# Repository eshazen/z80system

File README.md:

# z80system
Yet another home-brew z80 system

This project has diverged a lot from my original plan to build a
from-scratch portable Z80 system.  I may yet do that.  Meanwhile I
have an RC2014 system ~~running happily~~ which is very flaky.

## New thoughts in 2024

* See [DevLog2024](DevLog2024.md)

Ordered:

* SC131 complete kit
* 3x Z80 chips
* New EEPROM programmer PCB for Arduino Mega 2560
* A few more 32kx8 flash and some 512kx8 RAMs

Renewed interest in:

* A homebrew system with at least some retro features
* Rock-solid operation
* Two console options:
  * UART (FTDI) to PC
  * Keyboard and video (both UART also?)
* Easy interface for backup / file transfer (Ethernet, UART, other)
  (Ethernet ENC28J60, see below)
* IDE Hard drive (not sure why I'm obsessed with this!).  Could be SSD.
* VGA-class video, eventually with pixel graphics
* Possible ICom floppy interface (8255)

Not so interested in building all the peripherals (SIO, DMA, CTC) and
MMU so a Z180 seems like a nice option.  Will start with SC131 to get experience
with Z180.

### Buffered expansion bus

* I/O (any address above FF)
* Memory access at least 64k

Would like to minimise the gate delays in decoding the data bus enable,
so maybe just use A18, A19 for memory decode and A15 for IO decode.
74AHC139 + 74AHC32 = ~15ns max delay.

## What works now

* [FPGA_VGA](https://github.com/eshazen/z80system/tree/master/hardware/rc2014_vga) -
  RC2014 board hosting an FPGA module for VGA text video
* [FPGA_firmware](https://github.com/eshazen/vga_terminal) - firmware
  (Xilinx Vivado) for above
* [Keyboard](https://github.com/eshazen/z80system/tree/master/hardware/keyboard/minimal-60-v3) -
  60% keyboard with serial output
* [AVR_Code](https://github.com/eshazen/z80system/tree/master/hardware/keyboard/AVR_code) -
  AVR firmware for keyboard

## Moving Forward

After having fun with an RC2014 system for a bit, I found it to be too
flaky for serious use.  Not really interested in debugging it now.

2023 Proposed changes:

* Consider ECB SBC compatible design, but with Z80 CTC, DART, PIO
  instead of the Intel ones
* Add an IDE interface.  Seems as if an 8255 is a winner for this
* Maybe an ICOM Floppy interface, another 8255?
* Connect the CTC TO/TRG pins to a header (only)
* Add a 4.9152 osc and 74HC4040 as a simple baud rate generator
* Change the CPU clock to 4/8 MHz
* Add a network interface with ENC28J60 (see e.g. http://tuxgraphics.org/electronics/200905/embedded-tcp-ip-stack.shtml)

## Original notes

I'm starting (slowly, for now) on a home-brew Z80 general-purpose
computer.  I'm not very interested in the 8-bit gaming or
retro-Apple-Amiga world, but basically a re-creation of my development
system in 1984 or so.  It had a Z80B, I think 192k or 256k RAM, a
bunch of EEPROM configured as a read-only disk, 24x80 video with
attributes or color and a nice double-density floppy disk interface
with dual 3.5" floppy drives.  I'd like to enhance it with
decent-quality graphics, maybe 640x480 or 800x600 16-color (from a
palette).  Not sure yet about whether I want to fuss with a real
floppy system.  If it could be portable, as in a laptop, that would be
cool.

## CPU

This will be derived from my https://github.com/eshazen/retro-25
project.  Tentative feature list:

* Z80 CPU, DART, PIO
* AT28C256 32Kx8 EEPROM
* AS6C4008 512Kx8 SRAM
* Clocks: 8MHz osc /2 => 4MHz CPU clock or maybe faster
* Clocks: 1.8432MHz / 12 => 16X 9600 clock
* MAX232 or equiv; DB-25 for RS-232

## Video

Targeting at least 24x80 or greater VGA text with 640x480 pixel
resolution.  Eventually would like an in-period solution, maybe an
MC6845.  First version will use a Basys-3 FPGA board with this
opencores VHDL code:
https://opencores.org/projects/interface_vga80x40.  I bought a 5.7 in
640x480 LCD: <a
href="https://www.ebay.com/itm/5-7-LCD-Touchscreen-Display-640x480-OSD644803-6UFLWB-VGG644803-6UFLWB/112554850427?ssPageName=STRK%3AMEBIDX%3AIT&_trksid=p2057872.m2749.l2649">eBay</a>.
It has an annoying 0.5mm pitch flexi connector so I made a breakout
board:

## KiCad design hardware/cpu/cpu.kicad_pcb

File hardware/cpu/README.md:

# CPU board

Working in 'develop' as of 2025-08-26

Some thoughts:

* Change design rules to 6/6 mil so 2 tracks between 100 mil pads (done)
* Expansion connector should have more GNDs.  So maybe 50 pins (done)
* Should the buses be buffered?  Expansion buses? (nope)
* Integrated IDE interface?  Ditch the PIO for 8255 for this?
* Simpler baud rate generator?
* Ensure SIO pinout compatible with FTDI module/cable
 (or integrate FTDI modules on board)
 
Looking at IDE.  See for example [RC2014
IDE](https://rc2014.co.uk/modules/ide-hard-drive-module/).  This needs
16 data + 8 control signals.  Z80 PIO doesn't provide this!  However,
can operate with 8 bit data so maybe it's ok?

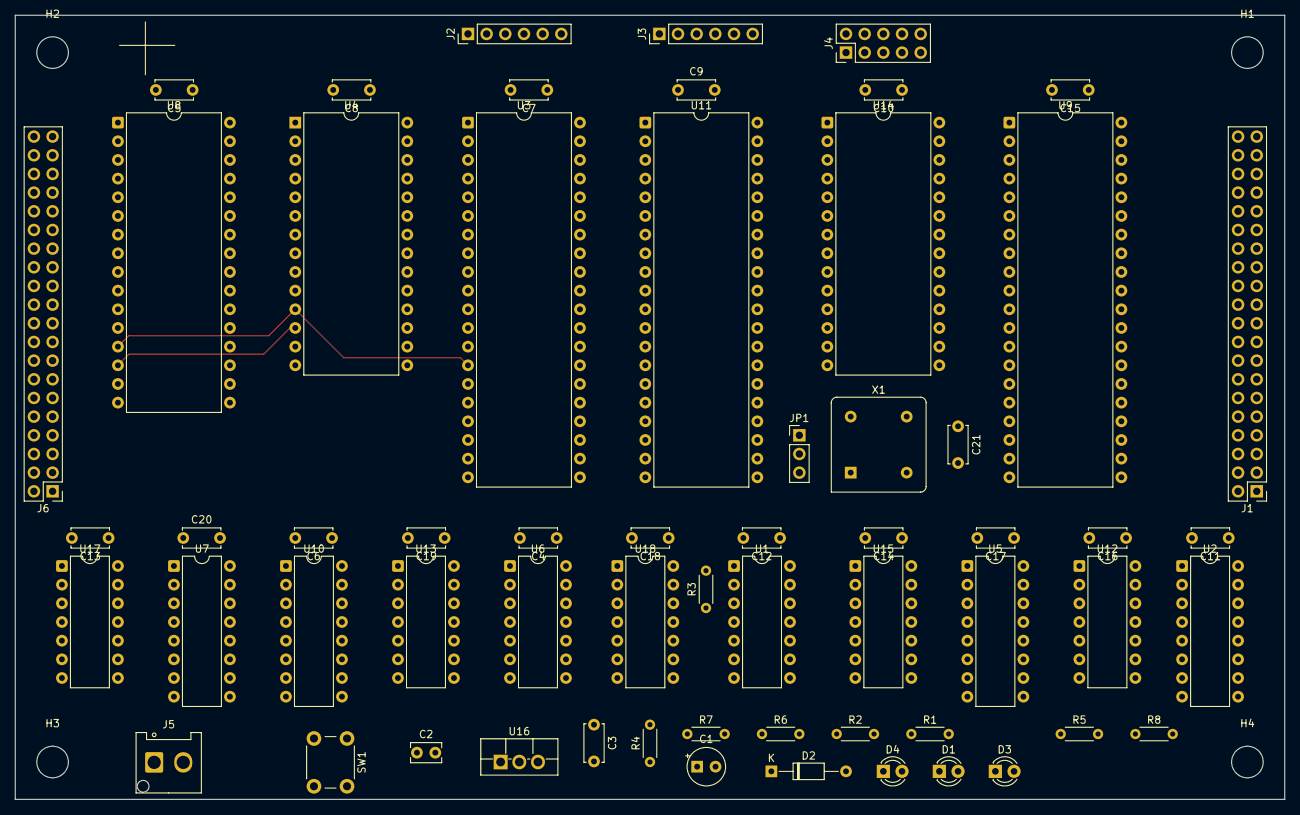
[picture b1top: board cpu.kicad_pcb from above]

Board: 4 copper layers, 172.7 x 106.7 mm, 64 parts (0 on the bottom side), 116 nets.

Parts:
C1: 10uF; CP_Radial_Tantal_D5.0mm_P2.50mm
C2: 0.33uF; C_Rect_L4.0mm_W2.5mm_P2.50mm
C3, C4, C5, C6, C7, C8, C9, C10, C11, C12, C13, C14, C15, C16, C17, C18, C19, C20, C21: 0.1uF; C_Disc_D5.0mm_W2.5mm_P5.00mm
D1, D3, D4: LED; LED_D3.0mm
D2: 1N914; D_DO-35_SOD27_P10.16mm_Horizontal
H1, H2, H3, H4: MountingHole; MountingHole_4.3mm_M4
J1, J6: Conn_02x20_Odd_Even; PinHeader_2x20_P2.54mm_Vertical
J2, J3: Conn_01x06; PinHeader_1x06_P2.54mm_Vertical
J4: Conn_02x05_Odd_Even; PinHeader_2x05_P2.54mm_Vertical
J5: Conn_01x02; Hirose_DF63-2P-3.96DSA_1x02_P3.96mm_Horizontal
JP1: JPR3; PinHeader_1x03_P2.54mm_Vertical
R1, R5, R6: 470; R_Axial_DIN0204_L3.6mm_D1.6mm_P5.08mm_Horizontal
R2, R7, R8: 4.7k; R_Axial_DIN0204_L3.6mm_D1.6mm_P5.08mm_Horizontal
R3: 1k; R_Axial_DIN0204_L3.6mm_D1.6mm_P5.08mm_Horizontal
R4: 10k; R_Axial_DIN0204_L3.6mm_D1.6mm_P5.08mm_Horizontal
SW1: SW_Push; SW_PUSH_6mm
U1, U17, U18: 74AS74; DIP-14_W7.62mm
U2: 74LS138; DIP-16_W7.62mm
U3: Z80CPU; DIP-40_W15.24mm
U4: AT28C256; DIP-28_W15.24mm
U5, U7: 74LS670; DIP-16_W7.62mm
U6: 74HC14; DIP-14_W7.62mm
U8: AS6C4008; DIP-32_W15.24mm
U9: Z80-PIO; DIP-40_W15.24mm
U10: 74LS157; DIP-16_W7.62mm
U11: Z80-DART; DIP-40_W15.24mm
U12, U15: 74HCT04; DIP-14_W7.62mm
U13: 74LS32; DIP-14_W7.62mm
U14: CTC; DIP-28_W15.24mm
U16: uA7805; TO-220F-3_Vertical
X1: 7.3728MHz; Oscillator_DIP-8

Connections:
+5V: C3.1, C4.1, C5.1, C6.1, C7.1, C8.1, C9.1, C10.1, C11.1, C12.1, C13.1, C14.1, C15.1, C16.1, C17.1, C18.1, C19.1, C20.1, C21.1, D1.2 (A), D2.2 (A), D3.2 (A), D4.2 (A), J6.35, J6.36, R3.2, R4.2, U1.1 (~R), U1.4 (~S), U1.10 (~S), U1.12 (D), U1.14 (VCC), U2.16 (VCC), U3.11 (VCC), U4.28 (VCC), U5.16 (VCC), U6.14 (VCC), U7.16 (VCC), U8.32 (VDD), U9.26 (+5V), U10.16 (VCC), U11.9 (+5V), U12.14 (VCC), U13.14 (VCC), U14.24 (VCC), U16.3 (OUT), U17.1 (~R), U17.4 (~S), U17.10 (~S), U17.13 (~R), U17.14 (VCC), U18.1 (~R), U18.4 (~S), U18.10 (~S), U18.13 (~R), U18.14 (VCC), X1.8 (Vcc)
/A0: J6.1, U3.30 (A0), U4.10 (A0), U5.14 (Wa), U7.14 (Wa), U8.12 (A0), U9.6 (B/nA), U11.33 (C/nD), U14.18 (CS0)
/A1: J6.3, U3.31 (A1), U4.9 (A1), U5.13 (Wb), U7.13 (Wb), U8.11 (A1), U9.5 (C/nD), U11.34 (B/nA), U14.19 (CS1)
/A2: J6.5, U2.1 (A0), U3.32 (A2), U4.8 (A2), U8.10 (A2)
/A3: J6.7, U2.2 (A1), U3.33 (A3), U4.7 (A3), U8.9 (A3)
/A4: J6.9, U2.3 (A2), U3.34 (A4), U4.6 (A4), U8.8 (A4)
/A5: J6.11, U3.35 (A5), U4.5 (A5), U8.7 (A5)
/A6: J6.13, U3.36 (A6), U4.4 (A6), U8.6 (A6)
/A7: J6.15, U3.37 (A7), U4.3 (A7), U8.5 (A7)
/A8: J6.17, U3.38 (A8), U4.25 (A8), U8.27 (A8)
/A9: J6.19, U3.39 (A9), U4.24 (A9), U8.26 (A9)
/A10: J6.21, U3.40 (A10), U4.21 (A10), U8.23 (A10)
/A11: J6.23, U3.1 (A11), U4.23 (A11), U8.25 (A11)
/A12: J6.25, U3.2 (A12), U4.2 (A12), U8.4 (A12)
/A13: J6.27, U3.3 (A13), U4.26 (A13), U8.28 (A13)
/A14: U3.4 (A14), U5.5 (Ra), U7.5 (Ra)
/A15: U3.5 (A15), U5.4 (Rb), U7.4 (Rb)
/BANK0: U7.10 (Q1), U8.3 (A14), U10.3 (I1a)
/BANK1: U7.9 (Q2), U8.31 (A15)
/BANK2: U7.7 (Q3), U8.2 (A16)
/BANK3: U7.6 (Q4), U8.1 (A17)
/BANK4: U5.10 (Q1), U8.30 (A18)
/BANK5: J6.29, U5.9 (Q2)
/BANK6: J6.31, U5.7 (Q3)
/BANK7: U5.6 (Q4), U10.6 (I1b), U10.13 (I1c)
/BAUD_A: U11.13 (nRxCA), U11.14 (nTxCA), U14.8 (TO1)
/BAUD_B: JP1.1 (A), U14.9 (TO2)
/CLK: J6.32, R3.1, U1.5 (Q), U3.6 (~CLK), U9.25 (CLK), U11.20 (CLK), U14.15 (CLK), U17.3 (C), U17.11 (C), U18.3 (C)
/CLK2: JP1.3 (B), U14.21 (TRG2), U14.22 (TRG1), U18.5 (Q)
/D0: J6.2, U3.14 (D0), U4.11 (D0), U7.15 (D1), U8.13 (I/O0), U9.19 (D0), U11.40 (D0), U14.25 (D0)
/D1: J6.4, U3.15 (D1), U4.12 (D1), U7.1 (D2), U8.14 (I/O1), U9.20 (D1), U11.1 (D1), U14.26 (D1)
/D2: J6.6, U3.12 (D2), U4.13 (D2), U7.2 (D3), U8.15 (I/O2), U9.1 (D2), U11.39 (D2), U14.27 (D2)
/D3: J6.8, U3.8 (D3), U4.15 (D3), U7.3 (D4), U8.17 (I/O3), U9.40 (D3), U11.2 (D3), U14.28 (D3)
/D4: J6.10, U3.7 (D4), U4.16 (D4), U5.15 (D1), U8.18 (I/O4), U9.39 (D4), U11.38 (D4), U14.1 (D4)
/D5: J6.12, U3.9 (D5), U4.17 (D5), U5.1 (D2), U8.19 (I/O5), U9.38 (D5), U11.3 (D5), U14.2 (D5)
/D6: J6.14, U3.10 (D6), U4.18 (D6), U5.2 (D3), U8.20 (I/O6), U9.3 (D6), U11.37 (D6), U14.3 (D6)
/D7: J6.16, U3.13 (D7), U4.19 (D7), U5.3 (D4), U8.21 (I/O7), U9.2 (D7), U11.4 (D7), U14.4 (D7)
/DIEO: U11.7 (IEO), U14.13 (IEI)
/PIEO: U9.22 (IEO), U11.6 (IEI)
/RA14: U4.1 (A14), U10.4 (Za)
/TO0: J4.3, U14.7 (TO0)
/TRG0: J4.1, U14.23 (TRG0)
/TRG3: J4.5, U14.20 (TRG3)
/nBANK: U2.12 (O3), U5.12 (~Ew), U7.12 (~Ew)
/nBOOT: U1.9 (Q), U10.1 (S), U15.3
/nCTC: U2.14 (O1), U14.16 (nCE)
/nDART: U2.13 (O2), U11.35 (nCE)
/nDCDA: J4.9, U11.19 (nDCDA)
/nDCDB: J4.2, U11.22 (nDCDB)
/nINT: J6.30, R2.1, U3.16 (~INT), U9.23 (nINT), U11.5 (nINT), U14.12 (nINT)
/nIO14: J6.26, U2.10 (O5)
/nIO18: J6.28, U2.9 (O6)
/nIORQ: J6.20, U2.5 (E2), U3.20 (~IORQ), U9.36 (nIORQ), U11.36 (nIORQ), U14.10 (nIORQ)
/nM1: J6.34, U3.27 (~M1), U9.37 (nM1), U11.8 (nM1), U14.14 (nM1)
/nMRD: U4.22 (~OE), U8.24 (~OE), U13.3
/nMREQ: J6.18, U3.19 (~MREQ), U13.1, U13.4, U13.10
/nMWR: U4.27 (nWE), U8.29 (~WE), U13.6
/nPIO: U2.15 (O0), U9.4 (nCE)
/nRAM: U8.22 (~CE), U10.7 (Zb)
/nRBOOT: U1.11 (C), U2.11 (O4)
/nRD: J6.22, U3.21 (~RD), U11.32 (nRD), U13.2
/nRIA: J4.7, U11.11 (nRIA)
/nROM: U4.20 (~CE), U13.9, U15.2
/nRST: J6.33, U1.13 (~R), U3.26 (~RESET), U6.4, U11.21 (nRESET), U14.17 (nRST)
/nWAIT: U3.24 (~WAIT), U13.11
/nWR: J6.24, U3.22 (~WR), U13.5
GND: C1.2, C2.2, C3.2, C4.2, C5.2, C6.2, C7.2, C8.2, C9.2, C10.2, C11.2, C12.2, C13.2, C14.2, C15.2, C16.2, C17.2, C18.2, C19.2, C20.2, C21.2, J1.2, J1.4, J1.6, J1.8, J1.10, J1.12, J1.14, J1.16, J1.18, J1.20, J1.22, J1.24, J1.26, J1.28, J1.30, J1.32, J1.34, J1.36, J1.38, J1.40, J2.6, J3.6, J4.4, J4.6, J4.8, J4.10, J5.2, J6.37, J6.38, J6.39, J6.40, SW1.2, U1.7 (GND), U2.4 (E1), U2.8 (GND), U3.29 (GND), U4.14 (GND), U5.8 (GND), U5.11 (~Er), U6.7 (GND), U7.8 (GND), U7.11 (~Er), U8.16 (GND), U9.11 (GND), U10.2 (I0a), U10.5 (I0b), U10.8 (GND), U10.14 (I0c), U10.15 (E), U11.31 (GND), U12.7 (GND), U13.7 (GND), U14.5 (GND), U16.2 (GND), U17.7 (GND), U18.7 (GND), U18.11 (C), X1.4 (GND)
unnamed: D1.1 (K), R1.2
unnamed: C1.1, D2.1 (K), R4.1, SW1.1, U6.1
unnamed: D3.1 (K), R5.2
unnamed: D4.1 (K), R6.2
unnamed: J1.1, U9.15 (A0), U15.9
unnamed: J1.3, U9.14 (A1)
unnamed: J1.5, U9.13 (A2)
unnamed: J1.7, U9.12 (A3)
unnamed: J1.9, U9.10 (A4)
unnamed: J1.11, U9.9 (A5)
unnamed: J1.13, U9.8 (A6)
unnamed: J1.15, U9.7 (A7)
unnamed: J1.17, U9.18 (ARDY)
unnamed: J1.19, U9.16 (nASTB)
unnamed: J1.21, U9.21 (BRDY)
unnamed: J1.23, U9.17 (nBSTB)
unnamed: J1.25, U9.27 (B0)
unnamed: J1.27, U9.28 (B1)
unnamed: J1.29, U9.29 (B2)
unnamed: J1.31, U9.30 (B3)
unnamed: J1.33, U9.31 (B4)
unnamed: J1.35, U9.32 (B5)
unnamed: J1.37, U9.33 (B6)
unnamed: J1.39, U9.34 (B7)
unnamed: J2.1, U11.16 (nDTRA)
unnamed: J2.2, U11.12 (RxDA)
unnamed: J2.3, U11.15 (TxDA)
unnamed: J2.5, U11.18 (nCTSA)
unnamed: J3.1, U11.25 (nDTRB)
unnamed: J3.2, U11.28 (RxDB)
unnamed: J3.3, U11.26 (TxDB)
unnamed: J3.5, U11.23 (nCTSB)
unnamed: C2.1, J5.1, U16.1 (IN)
unnamed: JP1.2 (C), U11.27 (nRxTxCB)
unnamed: R1.1, U15.6
unnamed: R5.1, U15.4
unnamed: R6.1, U15.8
unnamed: U1.3 (C), X1.5 (OUT)
unnamed: U1.2 (D), U1.6 (~Q)
unnamed: R8.1, U3.25 (~BUSRQ)
unnamed: U3.18 (~HALT), U15.5
unnamed: R7.1, U3.17 (~NMI)
unnamed: U6.2, U6.3
unnamed: U10.12 (Zc), U15.1
unnamed: U13.8, U17.2 (D)
unnamed: U13.13, U17.5 (Q), U17.12 (D)
unnamed: U13.12, U17.8 (~Q)
unnamed: U18.2 (D), U18.6 (~Q)
VCC: R2.2, R7.2, R8.2, U2.6 (E3), U9.24 (IEI)

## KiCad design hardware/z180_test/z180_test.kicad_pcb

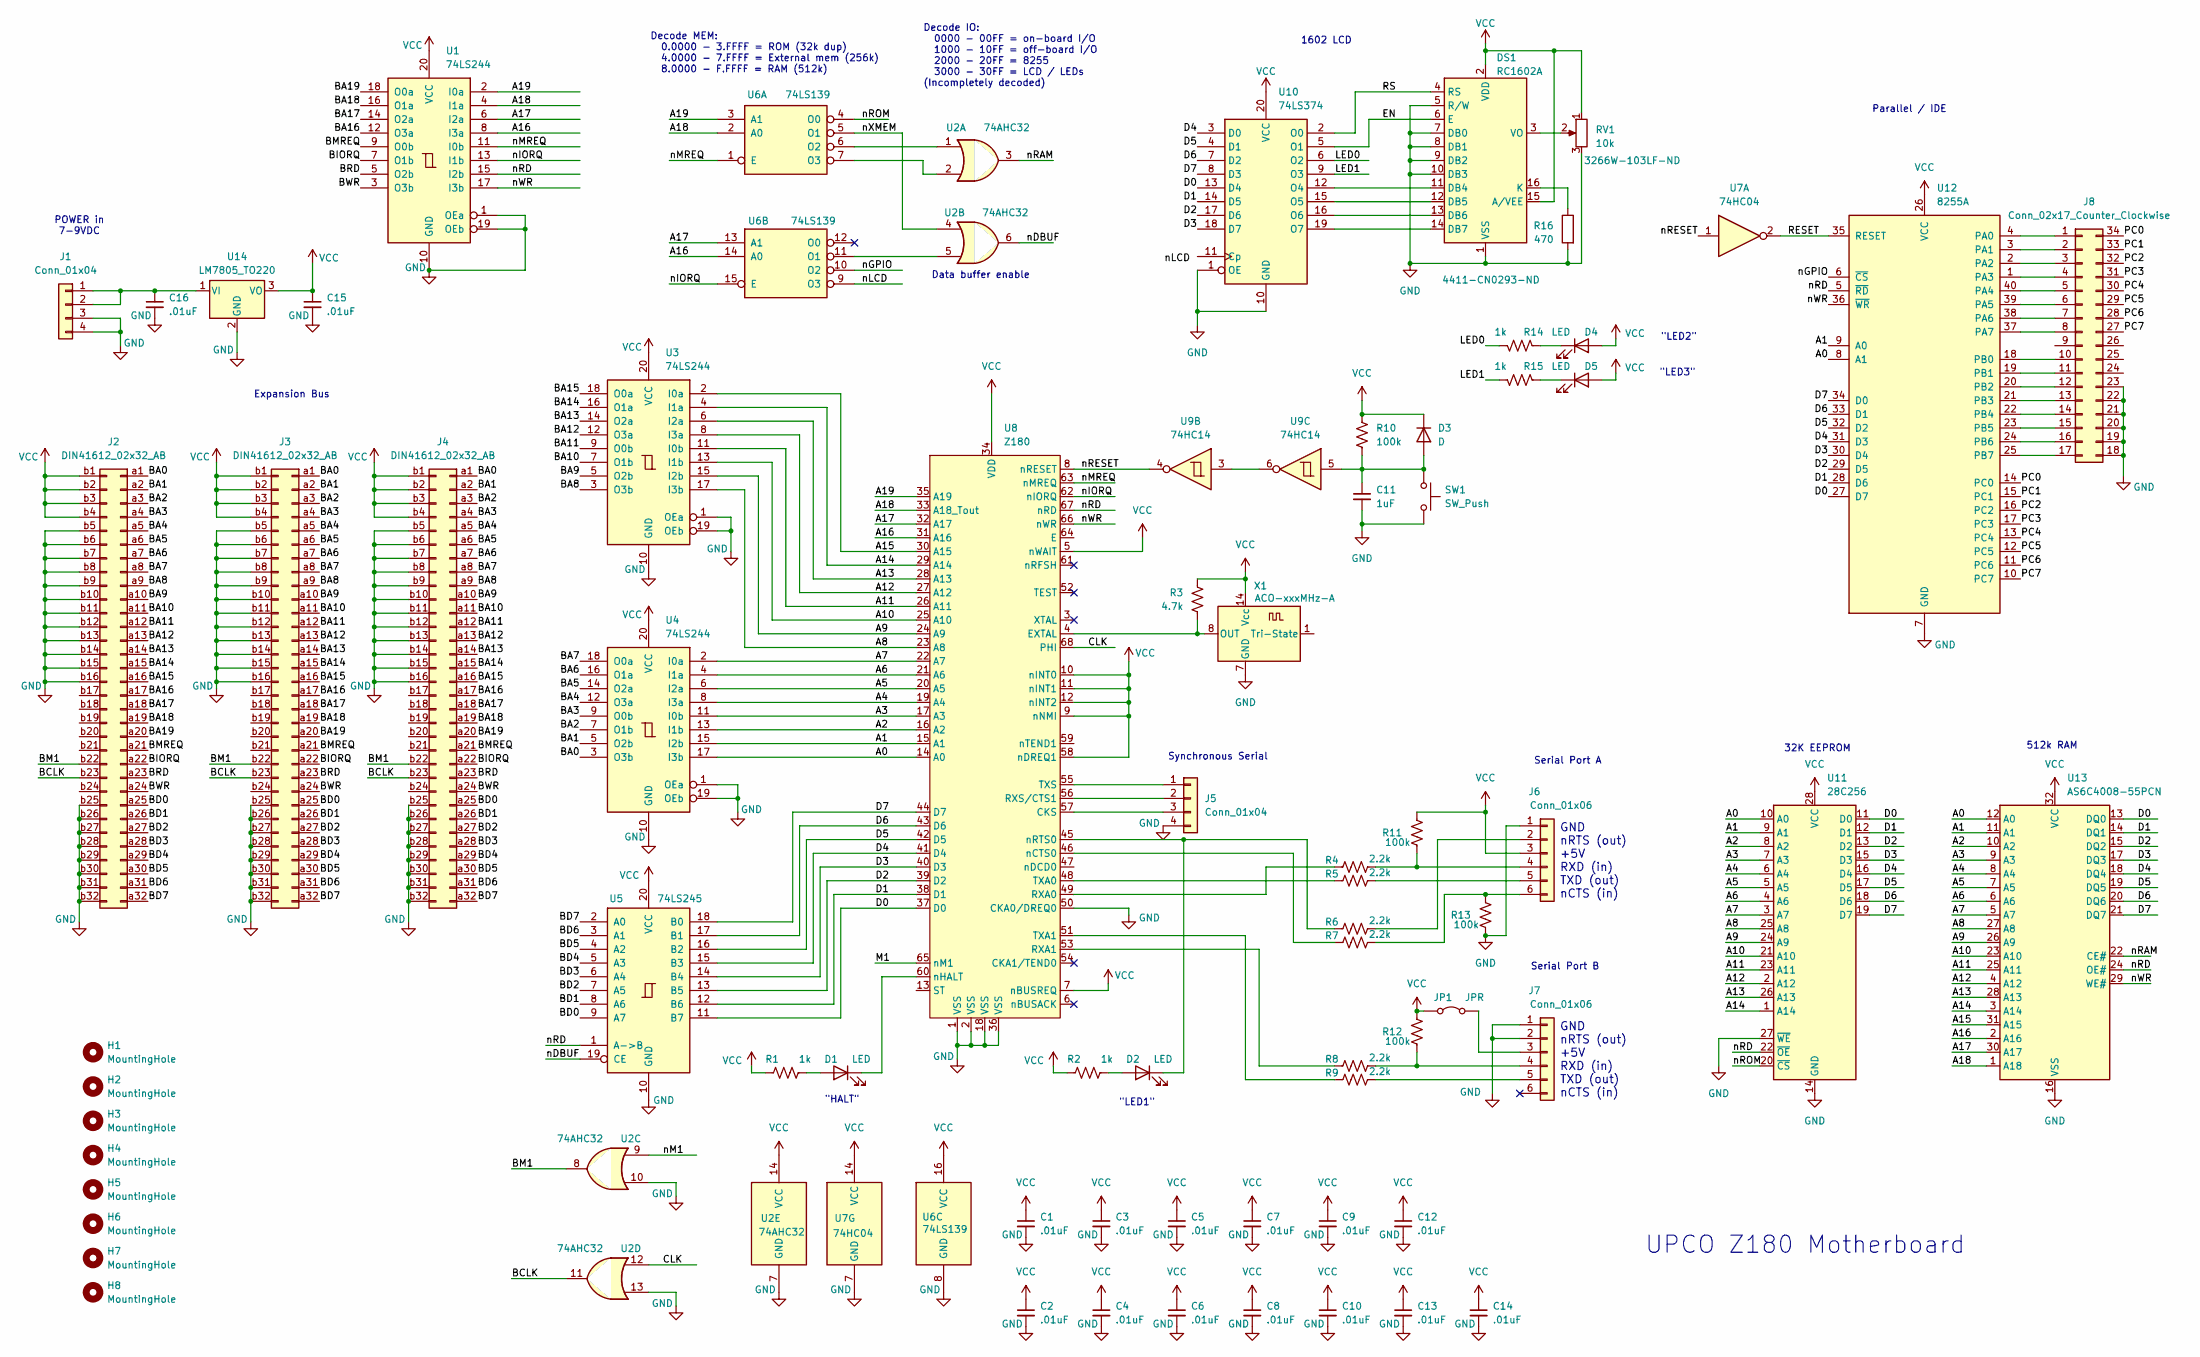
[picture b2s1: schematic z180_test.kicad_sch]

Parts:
C1, C2, C3, C4, C5, C6, C7, C8, C9, C10, C12, C13, C14, C15, C16: .01uF; C_Disc_D5.0mm_W2.5mm_P2.50mm
C11: 1uF; C_Disc_D5.0mm_W2.5mm_P2.50mm
D1, D2, D4, D5: LED; LED_D3.0mm
D3: D; D_T-1_P10.16mm_Horizontal
DS1: RC1602A; PinHeader_2x08_P2.54mm_Vertical
H1, H2, H3, H4, H5, H6, H7, H8: MountingHole; Mtg4-40
J1: Conn_01x04; Molex_KK-396_A-41791-0004_1x04_P3.96mm_Vertical
J2, J3, J4: DIN41612_02x32_AB; DIN41612_B_2x32_Female_Vertical_THT
J5: Conn_01x04; PinHeader_1x04_P2.54mm_Vertical
J6, J7: Conn_01x06; PinHeader_1x06_P2.54mm_Vertical
J8: Conn_02x17_Counter_Clockwise; PinHeader_2x17_P2.54mm_Vertical
JP1: JPR; PinHeader_1x02_P2.54mm_Vertical
R1, R2, R14, R15: 1k; R_Axial_DIN0207_L6.3mm_D2.5mm_P10.16mm_Horizontal
R3: 4.7k; R_Axial_DIN0207_L6.3mm_D2.5mm_P10.16mm_Horizontal
R4, R5, R6, R7, R8, R9: 2.2k; R_Axial_DIN0207_L6.3mm_D2.5mm_P10.16mm_Horizontal
R10, R11, R12, R13: 100k; R_Axial_DIN0207_L6.3mm_D2.5mm_P10.16mm_Horizontal
R16: 470; R_Axial_DIN0207_L6.3mm_D2.5mm_P10.16mm_Horizontal
RV1: 10k; Potentiometer_Bourns_3266W_Vertical
SW1: SW_Push; SW_Cherry_MX_1.00u_PCB
U1, U3, U4: 74LS244; DIP-20_W7.62mm
U2: 74AHC32; DIP-14_W7.62mm
U5: 74LS245; DIP-20_W7.62mm
U6: 74LS139; DIP-16_W7.62mm
U7: 74HC04; DIP-14_W7.62mm
U8: Z180; PLCC-68_THT-Socket
U9: 74HC14; DIP-14_W7.62mm
U10: 74LS374; DIP-20_W7.62mm
U11: 28C256; DIP-28_W15.24mm
U12: 8255A; DIP-40_W15.24mm
U13: AS6C4008-55PCN; DIP-32_W15.24mm
U14: LM7805_TO220; TO-220-3_Vertical
X1: ACO-xxxMHz-A; Oscillator_DIP-14

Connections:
/A0: U4.17 (I3b), U8.14 (A0), U11.10 (A0), U12.8 (A1), U13.12 (A0)
/A1: U4.15 (I2b), U8.15 (A1), U11.9 (A1), U12.9 (A0), U13.11 (A1)
/A2: U4.13 (I1b), U8.16 (A2), U11.8 (A2), U13.10 (A2)
/A3: U4.11 (I0b), U8.17 (A3), U11.7 (A3), U13.9 (A3)
/A4: U4.8 (I3a), U8.19 (A4), U11.6 (A4), U13.8 (A4)
/A5: U4.6 (I2a), U8.20 (A5), U11.5 (A5), U13.7 (A5)
/A6: U4.4 (I1a), U8.21 (A6), U11.4 (A6), U13.6 (A6)
/A7: U4.2 (I0a), U8.22 (A7), U11.3 (A7), U13.5 (A7)
/A8: U3.17 (I3b), U8.23 (A8), U11.25 (A8), U13.27 (A8)
/A9: U3.15 (I2b), U8.24 (A9), U11.24 (A9), U13.26 (A9)
/A10: U3.13 (I1b), U8.25 (A10), U11.21 (A10), U13.23 (A10)
/A11: U3.11 (I0b), U8.26 (A11), U11.23 (A11), U13.25 (A11)
/A12: U3.8 (I3a), U8.27 (A12), U11.2 (A12), U13.4 (A12)
/A13: U3.6 (I2a), U8.28 (A13), U11.26 (A13), U13.28 (A13)
/A14: U3.4 (I1a), U8.29 (A14), U11.1 (A14), U13.3 (A14)
/A15: U3.2 (I0a), U8.30 (A15), U13.31 (A15)
/A16: U1.8 (I3a), U6.14 (A0), U8.31 (A16), U13.2 (A16)
/A17: U1.6 (I2a), U6.13 (A1), U8.32 (A17), U13.30 (A17)
/A18: U1.4 (I1a), U6.2 (A0), U8.33 (A18_Tout), U13.1 (A18)
/A19: U1.2 (I0a), U6.3 (A1), U8.35 (A19)
/BA0: J2.a1, J3.a1, J4.a1, U4.3 (O3b)
/BA1: J2.a2, J3.a2, J4.a2, U4.5 (O2b)
/BA2: J2.a3, J3.a3, J4.a3, U4.7 (O1b)
/BA3: J2.a4, J3.a4, J4.a4, U4.9 (O0b)
/BA4: J2.a5, J3.a5, J4.a5, U4.12 (O3a)
/BA5: J2.a6, J3.a6, J4.a6, U4.14 (O2a)
/BA6: J2.a7, J3.a7, J4.a7, U4.16 (O1a)
/BA7: J2.a8, J3.a8, J4.a8, U4.18 (O0a)
/BA8: J2.a9, J3.a9, J4.a9, U3.3 (O3b)
/BA9: J2.a10, J3.a10, J4.a10, U3.5 (O2b)
/BA10: J2.a11, J3.a11, J4.a11, U3.7 (O1b)
/BA11: J2.a12, J3.a12, J4.a12, U3.9 (O0b)
/BA12: J2.a13, J3.a13, J4.a13, U3.12 (O3a)
/BA13: J2.a14, J3.a14, J4.a14, U3.14 (O2a)
/BA14: J2.a15, J3.a15, J4.a15, U3.16 (O1a)
/BA15: J2.a16, J3.a16, J4.a16, U3.18 (O0a)
/BA16: J2.a17, J3.a17, J4.a17, U1.12 (O3a)
/BA17: J2.a18, J3.a18, J4.a18, U1.14 (O2a)
/BA18: J2.a19, J3.a19, J4.a19, U1.16 (O1a)
/BA19: J2.a20, J3.a20, J4.a20, U1.18 (O0a)
/BCLK: J2.b23, J3.b23, J4.b23, U2.11
/BD0: J2.a25, J3.a25, J4.a25, U5.9 (A7)
/BD1: J2.a26, J3.a26, J4.a26, U5.8 (A6)
/BD2: J2.a27, J3.a27, J4.a27, U5.7 (A5)
/BD3: J2.a28, J3.a28, J4.a28, U5.6 (A4)
/BD4: J2.a29, J3.a29, J4.a29, U5.5 (A3)
/BD5: J2.a30, J3.a30, J4.a30, U5.4 (A2)
/BD6: J2.a31, J3.a31, J4.a31, U5.3 (A1)
/BD7: J2.a32, J3.a32, J4.a32, U5.2 (A0)
/BIORQ: J2.a22, J3.a22, J4.a22, U1.7 (O1b)
/BM1: J2.b22, J3.b22, J4.b22, U2.8
/BMREQ: J2.a21, J3.a21, J4.a21, U1.9 (O0b)
/BRD: J2.a23, J3.a23, J4.a23, U1.5 (O2b)
/BWR: J2.a24, J3.a24, J4.a24, U1.3 (O3b)
/CLK: U2.12, U8.68 (PHI)
/D0: U5.11 (B7), U8.37 (D0), U10.13 (D4), U11.11 (D0), U12.27 (D7), U13.13 (DQ0)
/D1: U5.12 (B6), U8.38 (D1), U10.14 (D5), U11.12 (D1), U12.28 (D6), U13.14 (DQ1)
/D2: U5.13 (B5), U8.39 (D2), U10.17 (D6), U11.13 (D2), U12.29 (D5), U13.15 (DQ2)
/D3: U5.14 (B4), U8.40 (D3), U10.18 (D7), U11.15 (D3), U12.30 (D4), U13.17 (DQ3)
/D4: U5.15 (B3), U8.41 (D4), U10.3 (D0), U11.16 (D4), U12.31 (D3), U13.18 (DQ4)
/D5: U5.16 (B2), U8.42 (D5), U10.4 (D1), U11.17 (D5), U12.32 (D2), U13.19 (DQ5)
/D6: U5.17 (B1), U8.43 (D6), U10.7 (D2), U11.18 (D6), U12.33 (D1), U13.20 (DQ6)
/D7: U5.18 (B0), U8.44 (D7), U10.8 (D3), U11.19 (D7), U12.34 (D0), U13.21 (DQ7)
/EN: DS1.6 (E), U10.5 (O1)
/LED0: R14.2, U10.6 (O2)
/LED1: R15.2, U10.9 (O3)
/M1: U8.65 (nM1)
/PC0: J8.34, U12.14 (PC0)
/PC1: J8.33, U12.15 (PC1)
/PC2: J8.32, U12.16 (PC2)
/PC3: J8.31, U12.17 (PC3)
/PC4: J8.30, U12.13 (PC4)
/PC5: J8.29, U12.12 (PC5)
/PC6: J8.28, U12.11 (PC6)
/PC7: J8.27, U12.10 (PC7)
/RESET: U7.2, U12.35 (RESET)
/RS: DS1.4 (RS), U10.2 (O0)
/nDBUF: U2.6, U5.19 (CE)
/nGPIO: U6.10 (O2), U12.6 (~CS)
/nIORQ: U1.13 (I1b), U6.15 (E), U8.62 (nIORQ)
/nLCD: U6.9 (O3)
/nM1: U2.9
/nMREQ: U1.11 (I0b), U6.1 (E), U8.63 (nMREQ)
/nRAM: U2.3, U13.22 (CE#)
/nRD: U1.15 (I2b), U5.1 (A->B), U8.67 (nRD), U11.22 (~OE), U12.5 (~RD), U13.24 (OE#)
/nRESET: U7.1, U8.8 (nRESET), U9.4
/nROM: U6.4 (O0), U11.20 (~CS)
/nWR: U1.17 (I3b), U8.66 (nWR), U12.36 (~WR), U13.29 (WE#)
/nXMEM: U2.4, U6.5 (O1)
GND: C1.2, C2.2, C3.2, C4.2, C5.2, C6.2, C7.2, C8.2, C9.2, C10.2, C11.2, C12.2, C13.2, C14.2, C15.2, C16.2, DS1.1 (VSS), DS1.5 (R/W), DS1.7 (DB0), DS1.8 (DB1), DS1.9 (DB2), DS1.10 (DB3), J1.3, J1.4, J2.b5, J2.b6, J2.b7, J2.b8, J2.b9, J2.b10, J2.b11, J2.b12, J2.b13, J2.b14, J2.b15, J2.b16, J2.b25, J2.b26, J2.b27, J2.b28, J2.b29, J2.b30, J2.b31, J2.b32, J3.b5, J3.b6, J3.b7, J3.b8, J3.b9, J3.b10, J3.b11, J3.b12, J3.b13, J3.b14, J3.b15, J3.b16, J3.b25, J3.b26, J3.b27, J3.b28, J3.b29, J3.b30, J3.b31, J3.b32, J4.b5, J4.b6, J4.b7, J4.b8, J4.b9, J4.b10, J4.b11, J4.b12, J4.b13, J4.b14, J4.b15, J4.b16, J4.b25, J4.b26, J4.b27, J4.b28, J4.b29, J4.b30, J4.b31, J4.b32, J5.4, J6.1, J7.1, J7.2, J8.18, J8.19, J8.20, J8.21, J8.22, J8.23, R13.1, R16.2, RV1.3, SW1.2, U1.1 (OEa), U1.10 (GND), U1.19 (OEb), U2.7 (GND), U2.10, U2.13, U3.1 (OEa), U3.10 (GND), U3.19 (OEb), U4.1 (OEa), U4.10 (GND), U4.19 (OEb), U5.10 (GND), U6.8 (GND), U7.7 (GND), U8.1 (VSS), U8.2 (VSS), U8.18 (VSS), U8.36 (VSS), U8.50 (CKA0/DREQ0), U10.1 (OE), U10.10 (GND), U11.14 (GND), U11.27 (~WE), U12.7 (GND), U13.16 (VSS), U14.2 (GND), X1.7 (GND)
unnamed: D1.2 (A), R1.2
unnamed: D1.1 (K), U8.60 (nHALT)
unnamed: D2.2 (A), R2.2
unnamed: D2.1 (K), R6.1, U8.45 (nRTS0)
unnamed: C11.1, D3.2 (A), R10.2, SW1.1, U9.5
unnamed: D4.1 (K), R14.1
unnamed: D5.1 (K), R15.1
unnamed: DS1.11 (DB4), U10.12 (O4)
unnamed: DS1.12 (DB5), U10.15 (O5)
unnamed: DS1.13 (DB6), U10.16 (O6)
unnamed: DS1.14 (DB7), U10.19 (O7)
unnamed: DS1.16 (K), R16.1
unnamed: DS1.3 (VO), RV1.2
unnamed: C16.1, J1.1, J1.2, U14.1 (VI)
unnamed: J5.1, U8.55 (TXS)
unnamed: J5.2, U8.56 (RXS/CTS1)
unnamed: J5.3, U8.57 (CKS)
unnamed: J6.2, R6.2
unnamed: J6.4, R4.2, R11.1
unnamed: J6.5, R5.2
unnamed: J6.6, R7.2, R13.2
unnamed: J7.3, JP1.2 (B)
unnamed: J7.4, R8.2, R12.1
unnamed: J7.5, R9.2
unnamed: J8.1, U12.4 (PA0)
unnamed: J8.2, U12.3 (PA1)
unnamed: J8.3, U12.2 (PA2)
unnamed: J8.4, U12.1 (PA3)
unnamed: J8.5, U12.40 (PA4)
unnamed: J8.6, U12.39 (PA5)
unnamed: J8.7, U12.38 (PA6)
unnamed: J8.8, U12.37 (PA7)
unnamed: J8.10, U12.18 (PB0)
unnamed: J8.11, U12.19 (PB1)
unnamed: J8.12, U12.20 (PB2)
unnamed: J8.13, U12.21 (PB3)
unnamed: J8.14, U12.22 (PB4)
unnamed: J8.15, U12.23 (PB5)
unnamed: J8.16, U12.24 (PB6)
unnamed: J8.17, U12.25 (PB7)
unnamed: U2.1, U6.6 (O2)
unnamed: U2.2, U6.7 (O3)
unnamed: U2.5, U6.11 (O1)
unnamed: R3.2, U8.4 (EXTAL), X1.8 (OUT)
unnamed: R4.1, U8.49 (RXA0)
unnamed: R8.1, U8.53 (RXA1)
unnamed: R5.1, U8.48 (TXA0)
unnamed: R9.1, U8.51 (TXA1)
unnamed: R7.1, U8.46 (nCTS0)
unnamed: U9.3, U9.6
VCC: C1.1, C2.1, C3.1, C4.1, C5.1, C6.1, C7.1, C8.1, C9.1, C10.1, C12.1, C13.1, C14.1, C15.1, D3.1 (K), D4.2 (A), D5.2 (A), DS1.2 (VDD), DS1.15 (A/VEE), J2.b1, J2.b2, J2.b3, J2.b4, J3.b1, J3.b2, J3.b3, J3.b4, J4.b1, J4.b2, J4.b3, J4.b4, J6.3, JP1.1 (A), R1.1, R2.1, R3.1, R10.1, R11.2, R12.2, RV1.1, U1.20 (VCC), U2.14 (VCC), U3.20 (VCC), U4.20 (VCC), U5.20 (VCC), U6.16 (VCC), U7.14 (VCC), U8.5 (nWAIT), U8.7 (nBUSREQ), U8.9 (nNMI), U8.10 (nINT0), U8.11 (nINT1), U8.12 (nINT2), U8.34 (VDD), U8.58 (nDREQ1), U10.20 (VCC), U11.28 (VCC), U12.26 (VCC), U13.32 (VCC), U14.3 (VO), X1.14 (Vcc)

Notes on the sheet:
"HALT"
Serial Port B
Serial Port A
UPCO Z180 Motherboard
GND nRTS (out) +5V RXD (in) TXD (out) nCTS (in)
Decode MEM: 0.0000 - 3.FFFF = ROM (32k dup) 4.0000 - 7.FFFF = External mem (256k) 8.0000 - F.FFFF = RAM (512k)
32K EEPROM
Parallel / IDE
POWER in 7-9VDC
1602 LCD
Decode IO: 0000 - 00FF = on-board I/O 1000 - 10FF = off-board I/O 2000 - 20FF = 8255 3000 - 30FF = LCD / LEDs (Incompletely decoded)
512k RAM
Data buffer enable
"LED1"
Expansion Bus
"LED3"
"LED2"
Synchronous Serial

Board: 4 copper layers, 72 parts (0 on the bottom side), 138 nets, no tracks yet.

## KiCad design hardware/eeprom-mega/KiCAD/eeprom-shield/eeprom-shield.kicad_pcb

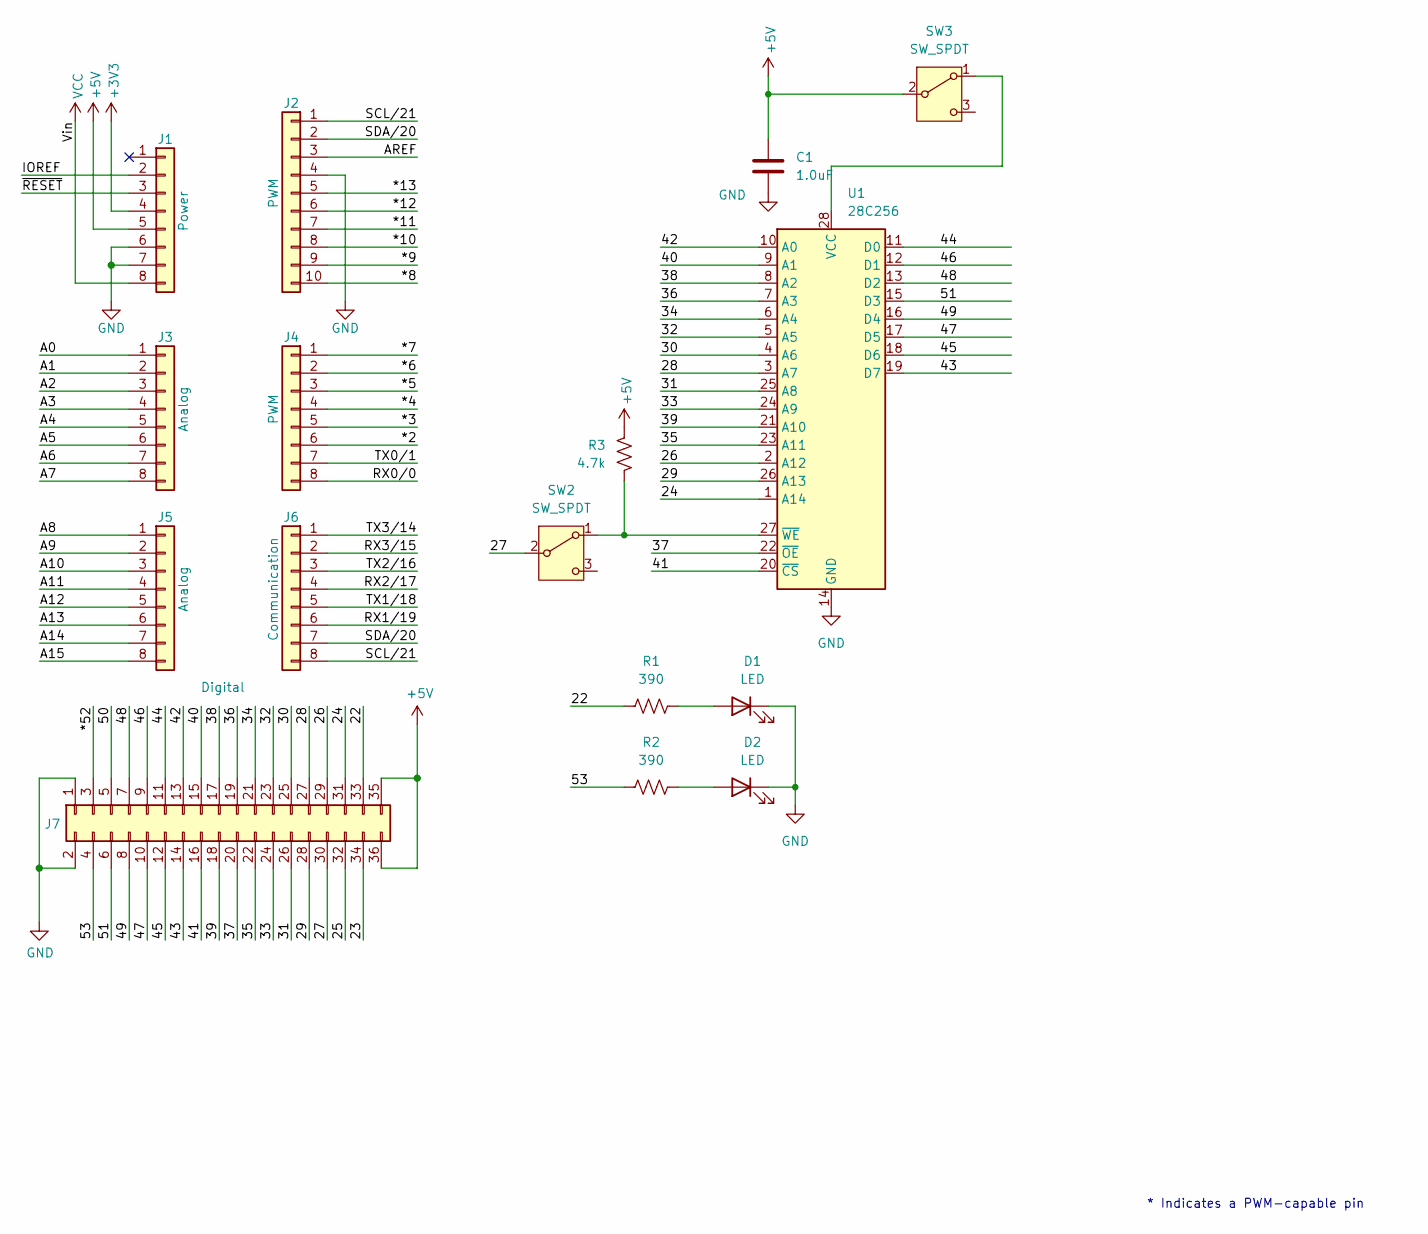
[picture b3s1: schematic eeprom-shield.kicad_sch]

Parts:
C1: 1.0uF; C_Disc_D7.5mm_W2.5mm_P5.00mm
D1, D2: LED; LED_D3.0mm
J1: Power; PinSocket_1x08_P2.54mm_Vertical
J2: PWM; PinSocket_1x10_P2.54mm_Vertical
J3, J5: Analog; PinSocket_1x08_P2.54mm_Vertical
J4: PWM; PinSocket_1x08_P2.54mm_Vertical
J6: Communication; PinSocket_1x08_P2.54mm_Vertical
J7: Digital; PinSocket_2x18_P2.54mm_Vertical
R1, R2: 390; R_Axial_DIN0204_L3.6mm_D1.6mm_P7.62mm_Horizontal
R3: 4.7k; R_Axial_DIN0204_L3.6mm_D1.6mm_P7.62mm_Horizontal
SW2, SW3: SW_SPDT; sw_spdt_2.54mm
U1: 28C256; DIP_Socket-28_W11.9_W12.7_W15.24_W17.78_W18.5_3M_228-1277-0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

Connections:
+3V3: J1.4
+5V: C1.1, J1.5, J7.35, J7.36, R3.2, SW3.2 (B)
/22: J7.33, R1.1
/23: J7.34
/24: J7.31, U1.1 (A14)
/25: J7.32
/26: J7.29, U1.2 (A12)
/27: J7.30, SW2.2 (B)
/28: J7.27, U1.3 (A7)
/29: J7.28, U1.26 (A13)
/30: J7.25, U1.4 (A6)
/31: J7.26, U1.25 (A8)
/32: J7.23, U1.5 (A5)
/33: J7.24, U1.24 (A9)
/34: J7.21, U1.6 (A4)
/35: J7.22, U1.23 (A11)
/36: J7.19, U1.7 (A3)
/37: J7.20, U1.22 (~OE)
/38: J7.17, U1.8 (A2)
/39: J7.18, U1.21 (A10)
/40: J7.15, U1.9 (A1)
/41: J7.16, U1.20 (~CS)
/42: J7.13, U1.10 (A0)
/43: J7.14, U1.19 (D7)
/44: J7.11, U1.11 (D0)
/45: J7.12, U1.18 (D6)
/46: J7.9, U1.12 (D1)
/47: J7.10, U1.17 (D5)
/48: J7.7, U1.13 (D2)
/49: J7.8, U1.16 (D4)
/50: J7.5
/51: J7.6, U1.15 (D3)
/53: J7.4, R2.1
/*2: J4.6
/*3: J4.5
/*4: J4.4
/*5: J4.3
/*6: J4.2
/*7: J4.1
/*8: J2.10
/*9: J2.9
/*10: J2.8
/*11: J2.7
/*12: J2.6
/*13: J2.5
/*52: J7.3
/A0: J3.1
/A1: J3.2
/A2: J3.3
/A3: J3.4
/A4: J3.5
/A5: J3.6
/A6: J3.7
/A7: J3.8
/A8: J5.1
/A9: J5.2
/A10: J5.3
/A11: J5.4
/A12: J5.5
/A13: J5.6
/A14: J5.7
/A15: J5.8
/AREF: J2.3
/IOREF: J1.2
/RX0/0: J4.8
/RX1/19: J6.6
/RX2/17: J6.4
/RX3/15: J6.2
/SCL/21: J2.1, J6.8
/SDA/20: J2.2, J6.7
/TX0/1: J4.7
/TX1/18: J6.5
/TX2/16: J6.3
/TX3/14: J6.1
/~RESET: J1.3
GND: C1.2, D1.1 (K), D2.1 (K), J1.6, J1.7, J2.4, J7.1, J7.2, U1.14 (GND)
unnamed: D1.2 (A), R1.2
unnamed: D2.2 (A), R2.2
unnamed: R3.1, SW2.1 (A), U1.27 (~WE)
unnamed: SW3.1 (A), U1.28 (VCC)
VCC: J1.8

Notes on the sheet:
* Indicates a PWM-capable pin

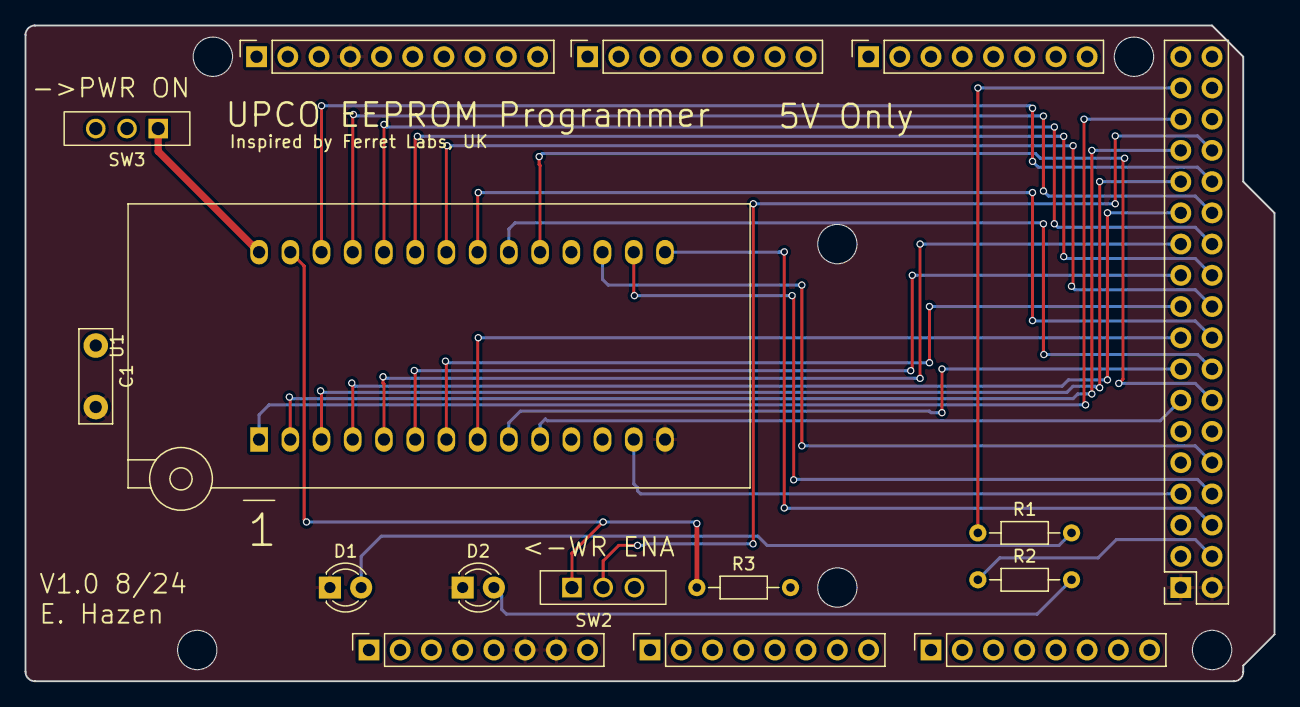
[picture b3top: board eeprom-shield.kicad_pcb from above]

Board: 2 copper layers, 101.6 x 53.3 mm, 22 parts (0 on the bottom side), 36 nets.

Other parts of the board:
MH1, MH2, MH3, MH4, MH5, MH6: MountingHole_3.2mm

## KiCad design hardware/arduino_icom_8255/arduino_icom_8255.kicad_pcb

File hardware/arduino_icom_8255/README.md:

# arduino_icom_8255

This is an Arduino shield with an 82C55 Programmable Peripheral Interface (PPI)
chip.  20 and 26-pin ribbon cable pinouts match (hopefully) the iCOM interface.

Unfortunately I put the Arduino shield footprint on the wrong side (front)
while it should be on the back, so the board has to mount component-side
down on the Arduino.  This is fine with tall headers, but no good for the
ribbon cables, so will need to put headers on the back and do the old parity
flip thing with wire-wrap connectors.

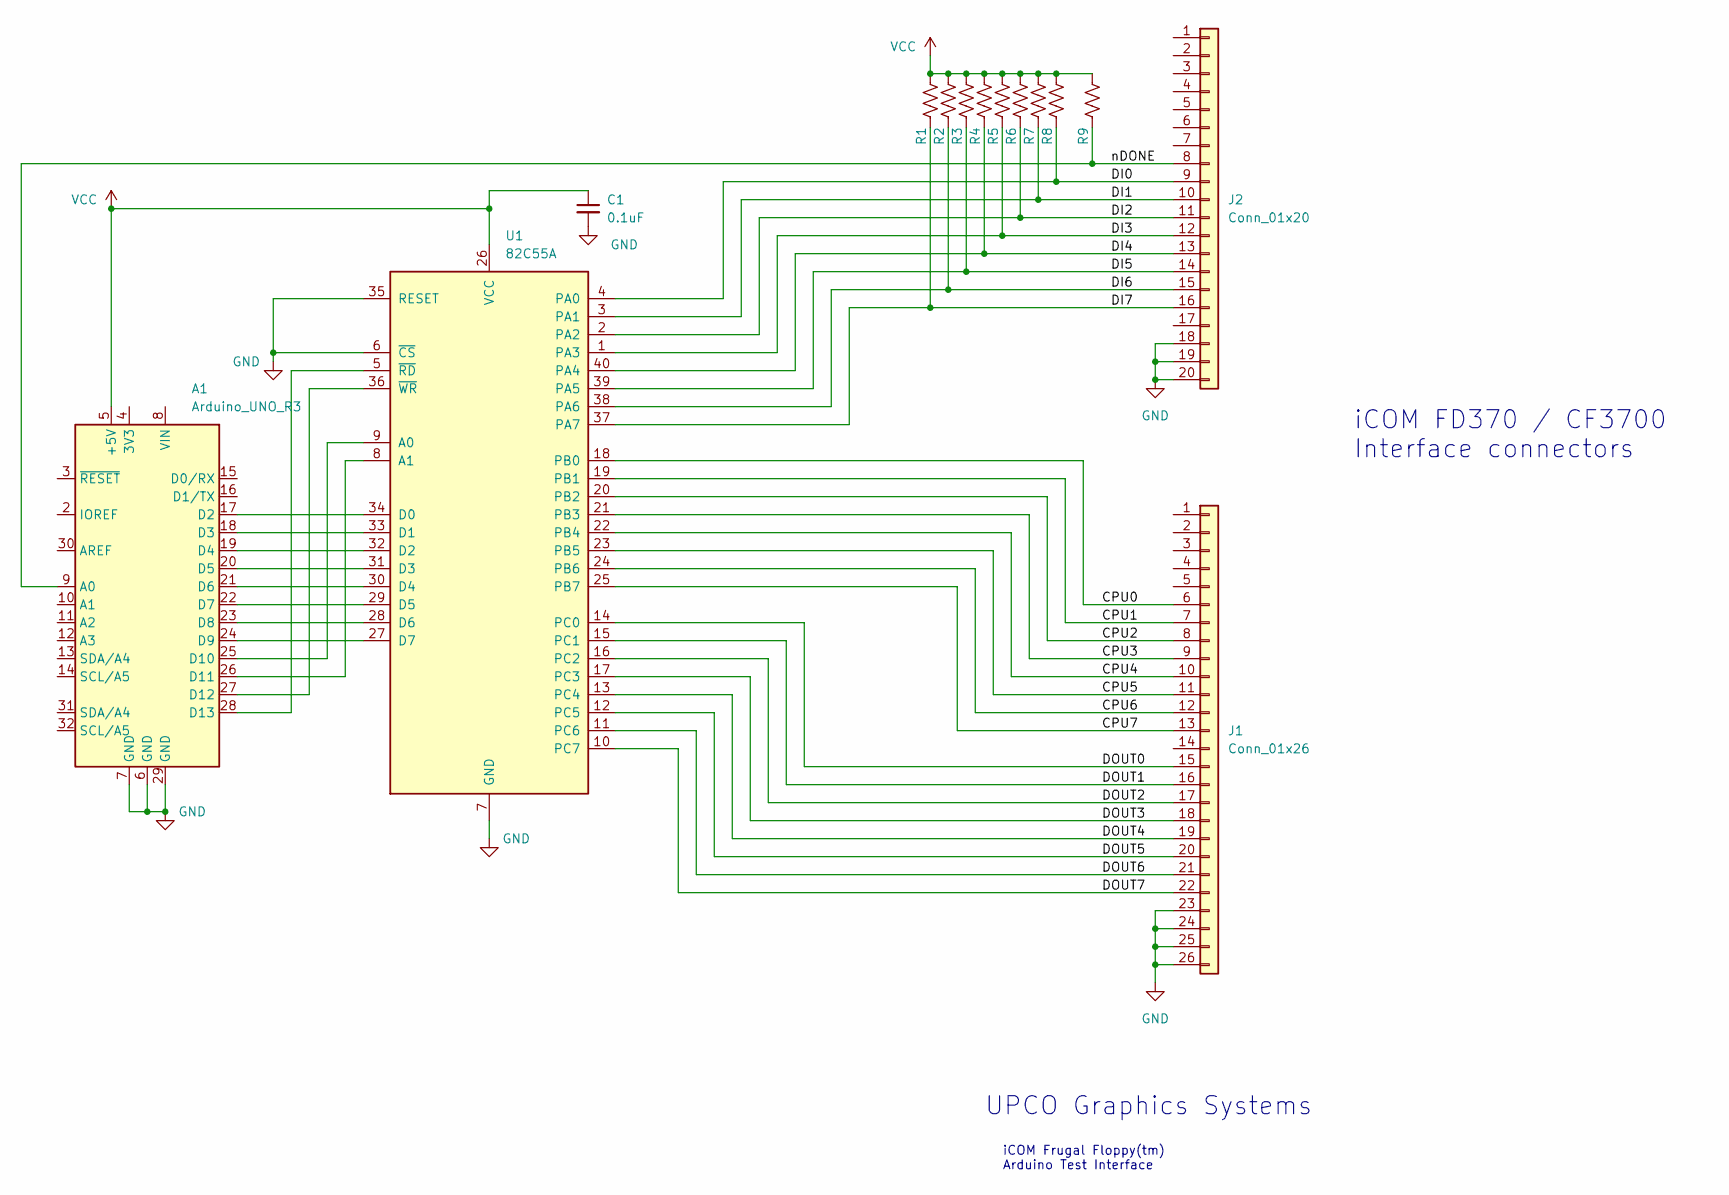
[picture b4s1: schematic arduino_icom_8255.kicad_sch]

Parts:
A1: Arduino_UNO_R3
C1: 0.1uF; C_Disc_D3.0mm_W1.6mm_P2.50mm
J1: Conn_01x26; PinHeader_2x13_P2.54mm_Vertical
J2: Conn_01x20; PinHeader_2x10_P2.54mm_Vertical
R1, R2, R3, R4, R5, R6, R7, R8, R9: 1k; R_Axial_DIN0309_L9.0mm_D3.2mm_P2.54mm_Vertical
U1: 82C55A; DIP-40_W15.24mm

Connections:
/CPU0: J1.6, U1.18 (PB0)
/CPU1: J1.7, U1.19 (PB1)
/CPU2: J1.8, U1.20 (PB2)
/CPU3: J1.9, U1.21 (PB3)
/CPU4: J1.10, U1.22 (PB4)
/CPU5: J1.11, U1.23 (PB5)
/CPU6: J1.12, U1.24 (PB6)
/CPU7: J1.13, U1.25 (PB7)
/DI0: J2.9, R8.2, U1.4 (PA0)
/DI1: J2.10, R7.2, U1.3 (PA1)
/DI2: J2.11, R6.2, U1.2 (PA2)
/DI3: J2.12, R5.2, U1.1 (PA3)
/DI4: J2.13, R4.2, U1.40 (PA4)
/DI5: J2.14, R3.2, U1.39 (PA5)
/DI6: J2.15, R2.2, U1.38 (PA6)
/DI7: J2.16, R1.2, U1.37 (PA7)
/DOUT0: J1.15, U1.14 (PC0)
/DOUT1: J1.16, U1.15 (PC1)
/DOUT2: J1.17, U1.16 (PC2)
/DOUT3: J1.18, U1.17 (PC3)
/DOUT4: J1.19, U1.13 (PC4)
/DOUT5: J1.20, U1.12 (PC5)
/DOUT6: J1.21, U1.11 (PC6)
/DOUT7: J1.22, U1.10 (PC7)
/nDONE: A1.9 (A0), J2.8, R9.2
GND: A1.6 (GND), A1.7 (GND), A1.29 (GND), C1.2, J1.23, J1.24, J1.25, J1.26, J2.18, J2.19, J2.20, U1.6 (~CS), U1.7 (GND), U1.35 (RESET)
unnamed: A1.17 (D2), U1.34 (D0)
unnamed: A1.18 (D3), U1.33 (D1)
unnamed: A1.19 (D4), U1.32 (D2)
unnamed: A1.20 (D5), U1.31 (D3)
unnamed: A1.21 (D6), U1.30 (D4)
unnamed: A1.22 (D7), U1.29 (D5)
unnamed: A1.23 (D8), U1.28 (D6)
unnamed: A1.24 (D9), U1.27 (D7)
unnamed: A1.25 (D10), U1.9 (A0)
unnamed: A1.26 (D11), U1.8 (A1)
unnamed: A1.27 (D12), U1.36 (~WR)
unnamed: A1.28 (D13), U1.5 (~RD)
VCC: A1.5 (+5V), C1.1, R1.1, R2.1, R3.1, R4.1, R5.1, R6.1, R7.1, R8.1, R9.1, U1.26 (VCC)

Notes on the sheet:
UPCO Graphics Systems
iCOM FD370 / CF3700 Interface connectors
iCOM Frugal Floppy(tm) Arduino Test Interface
